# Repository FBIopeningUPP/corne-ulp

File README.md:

# AERIX-ULP

AERIX-ULP is a low-profile split mechanical keyboard with a custom layout.
It is designed around Cherry MX Ultra Low Profile switches and uses a separate
wireless controller and battery-powered electronics on each half.

The board includes:

- 42 keys with per-key diodes
- Wireless nRF52 modules
- USB-C charging and programming
- Separate Li-Po battery support for each half
- 3.0 V regulation
- LCD connectors
- SWD programming and test points
- No 3D-printed case; the underside uses rubber grip dots

AERIX-ULP is a custom keyboard design rather than a Corne-layout derivative.
This project includes the schematics, PCB layout, component library, and
schematics, PCB layout, component library, and production files.

## Board views

- [Main schematic source](hardware/split/split.kicad_sch)
- [Left-half schematic source](hardware/split/left.kicad_sch)
- [Right-half schematic source](hardware/split/right.kicad_sch)
- [Switch matrix schematic source](hardware/split/switch.kicad_sch)
- [PCB layout source](hardware/split/split.kicad_pcb)

schematics and layout.

## Hardware Development

1. Open the KiCad project in `hardware/split/`.
2. Review the custom-layout schematics and PCB layout.
3. Continue placement, routing, and electrical validation in KiCad.
4. Generate fabrication files when the hardware design is ready.
5. Use the production BOM and placement files for assembly.

## Assembly and first power-up

1. Assemble one half and check component orientation.
2. Inspect for solder bridges and shorts.
3. Power it from USB with the battery disconnected.
4. Check `VDD_SYS` and the 3.0 V rail.
5. Connect the battery after the rail check passes.
6. Flash ZMK over SWD and test every key.
7. Repeat for the other half, then test pairing and the inter-half connection.

### Firmware flashing over SWD

Use a 3.3 V-compatible J-Link or CMSIS-DAP probe.

1. Connect `VTref`, `GND`, `SWDIO`, `SWCLK`, and `nRESET` to the matching
   `VDD_SYS`, `GND`, `SWDIO`, `SWDCLK`, and `RESET` test points.
2. Build ZMK and place the generated `firmware.hex` beside `nrfjprog`.
3. Power the half and run:

   ```text
   nrfjprog --program firmware.hex --verify --reset
   ```

Repeat for the other half.

## Source Files

- **Main schematic:** `hardware/split/split.kicad_sch`
- **Left-side schematic:** `hardware/split/left.kicad_sch`
- **Right-side schematic:** `hardware/split/right.kicad_sch`
- **Switch schematic:** `hardware/split/switch.kicad_sch`
- **PCB layout:** `hardware/split/split.kicad_pcb`
- **KiCad project:** `hardware/split/split.kicad_pro`
- **Custom symbols and footprints:** `lib/`
- **ZMK firmware:** `firmware/`

## Production Bill of Materials

The production BOM is available here: [production/bom.csv](production/bom.csv).
The placement files are also available in the [`production/`](production/)
folder:

- [designators.csv](production/designators.csv)
- [positions.csv](production/positions.csv)

The BOM contains **33 line items** and **146 individual parts** for one
complete board assembly. It includes both keyboard halves.

| Designator | Footprint | Qty | Value | LCSC Part # / sourcing |
|---|---|---:|---|---|
| C1, C101, C104, C105, C4, C5 | 0603 | 6 | 100n | [LCSC search](https://www.lcsc.com/search?q=0603%20100nF) |
| C102, C109, C2, C9 | 0603 | 4 | 2.2uF | [LCSC search](https://www.lcsc.com/search?q=0603%202.2uF) |
| C103, C3 | CAP-SMD_L1.6-W0.8-RD | 2 | 4.7uF 6.3V polymer tantalum | [C2158419](https://www.lcsc.com/product-detail/C2158419.html) |
| C106, C107, C6, C7 | 0402 | 4 | 1uF | [LCSC search](https://www.lcsc.com/search?q=0402%201uF) |
| C108, C8 | 0402 | 2 | 560pF | [LCSC search](https://www.lcsc.com/search?q=0402%20560pF) |
| D1, D101 | SOD-323_L1.7-W1.3-LS2.7-RD | 2 | 1N5819WS | [C489147](https://www.lcsc.com/product-detail/C489147.html) |
| D2-D22, D102-D122 | SOD-523_L1.2-W0.8-LS1.6-RD | 42 | 1N4148WT-7 | [C83482](https://www.lcsc.com/product-detail/C83482.html) |
| J1, J101 | FFC-SMD_10P-P0.50_FH34SRJ-10S-0.5SH | 2 | LS011B7DH03_FPC | [C324723](https://www.lcsc.com/product-detail/C324723.html) |
| OSC1, OSC101 | OSC-SMD_4P-L3.2-W1.5 | 2 | X1B0002110001 | [C256005](https://www.lcsc.com/product-detail/C256005.html) |
| Q2, Q102 | SOT-23-3_L3.0-W1.7-P0.95-LS2.9-BR | 2 | AO3407 | [C351408](https://www.lcsc.com/product-detail/C351408.html) |
| R1, R101, R102, R2 | 0402 | 4 | 5.1k | [LCSC search](https://www.lcsc.com/search?q=0402%205.1k) |
| R3, R8, R103, R108 | 0402 | 4 | 100k | [LCSC search](https://www.lcsc.com/search?q=0402%20100k) |
| R4, R104 | 0402 | 2 | 33.2k | [LCSC search](https://www.lcsc.com/search?q=0402%2033.2k) |
| R6, R7, R106, R107 | 0402 | 4 | 820k | [LCSC search](https://www.lcsc.com/search?q=0402%20820k) |
| SW1-SW21, SW101-SW121 | Cherry_ULP_SMD | 42 | Cherry_ULP_SMD | [Cherry MX ULP](https://www.cherry.de/en-us/products/switches/mx-ultra-low-profile) |
| TP1 | TestPoint_Pad_D1.5mm | 1 | L_VDD_SYS | [LCSC search](https://www.lcsc.com/search?q=1.5mm%20test%20point%20pad) |
| TP2, TP7 | TestPoint_Pad_D1.5mm | 2 | L_GND | [LCSC search](https://www.lcsc.com/search?q=1.5mm%20test%20point%20pad) |
| TP3 | TestPoint_Pad_D1.5mm | 1 | L_SWDIO | [LCSC search](https://www.lcsc.com/search?q=1.5mm%20test%20point%20pad) |
| TP4 | TestPoint_Pad_D1.5mm | 1 | L_SWDCLK | [LCSC search](https://www.lcsc.com/search?q=1.5mm%20test%20point%20pad) |
| TP5 | TestPoint_Pad_D1.5mm | 1 | L_RESET | [LCSC search](https://www.lcsc.com/search?q=1.5mm%20test%20point%20pad) |
| TP6 | TestPoint_Pad_D2.0mm | 1 | L_VBAT | [LCSC search](https://www.lcsc.com/search?q=2mm%20test%20point%20pad) |
| TP101 | TestPoint_Pad_D1.5mm | 1 | R_VDD_SYS | [LCSC search](https://www.lcsc.com/search?q=1.5mm%20test%20point%20pad) |
| TP102, TP107 | TestPoint_Pad_D1.5mm | 2 | R_GND | [LCSC search](https://www.lcsc.com/search?q=1.5mm%20test%20point%20pad) |
| TP103 | TestPoint_Pad_D1.5mm | 1 | R_SWDIO | [LCSC search](https://www.lcsc.com/search?q=1.5mm%20test%20point%20pad) |
| TP104 | TestPoint_Pad_D1.5mm | 1 | R_SWDCLK | [LCSC search](https://www.lcsc.com/search?q=1.5mm%20test%20point%20pad) |
| TP105 | TestPoint_Pad_D1.5mm | 1 | R_RESET | [LCSC search](https://www.lcsc.com/search?q=1.5mm%20test%20point%20pad) |
| TP106 | TestPoint_Pad_D2.0mm | 1 | R_VBAT | [LCSC search](https://www.lcsc.com/search?q=2mm%20test%20point%20pad) |
| U1, U101 | WIRELM-SMD_E73-2G4M08S1C | 2 | E73-2G4M08S1C | [C356849](https://www.lcsc.com/product-detail/C356849.html) |
| U2, U102 | SOT-23-5_L3.0-W1.7-P0.95-LS2.8-BL | 2 | TP4054 | [C32574](https://www.lcsc.com/product-detail/C32574.html) |
| U3, U103 | SOT-23-5 | 2 | MIC5219-3.0YM5 | [LCSC search](https://www.lcsc.com/search?q=MIC5219-3.0YM5) |
| USB1, USB101 | USB-C-SMD_SHOU_TYPE-C-16P-CB1.6 | 2 | TYPE-C 16P CB1.6 073 | [C2906290](https://www.lcsc.com/product-detail/C2906290.html) |

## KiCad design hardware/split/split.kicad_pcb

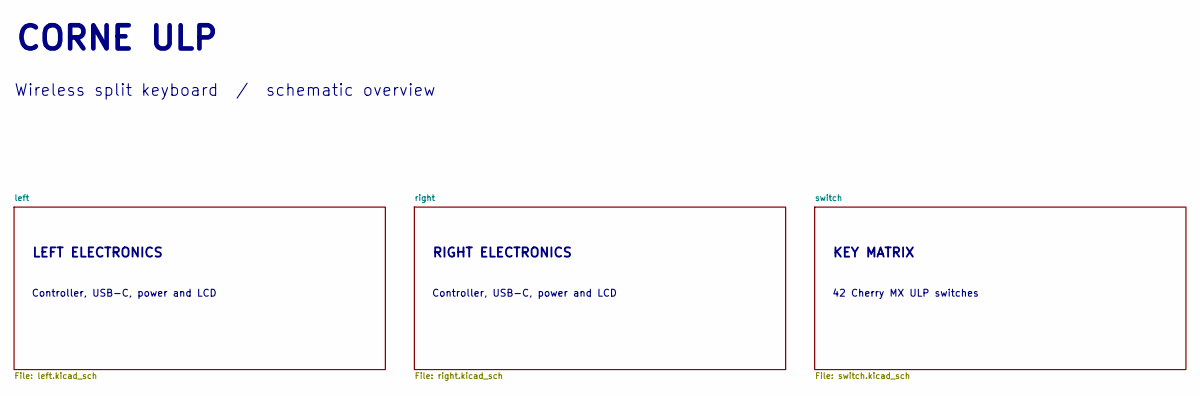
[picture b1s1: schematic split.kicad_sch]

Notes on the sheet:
Controller, USB-C, power and LCD
CORNE ULP
42 Cherry MX ULP switches
Wireless split keyboard / schematic overview
RIGHT ELECTRONICS
LEFT ELECTRONICS
KEY MATRIX

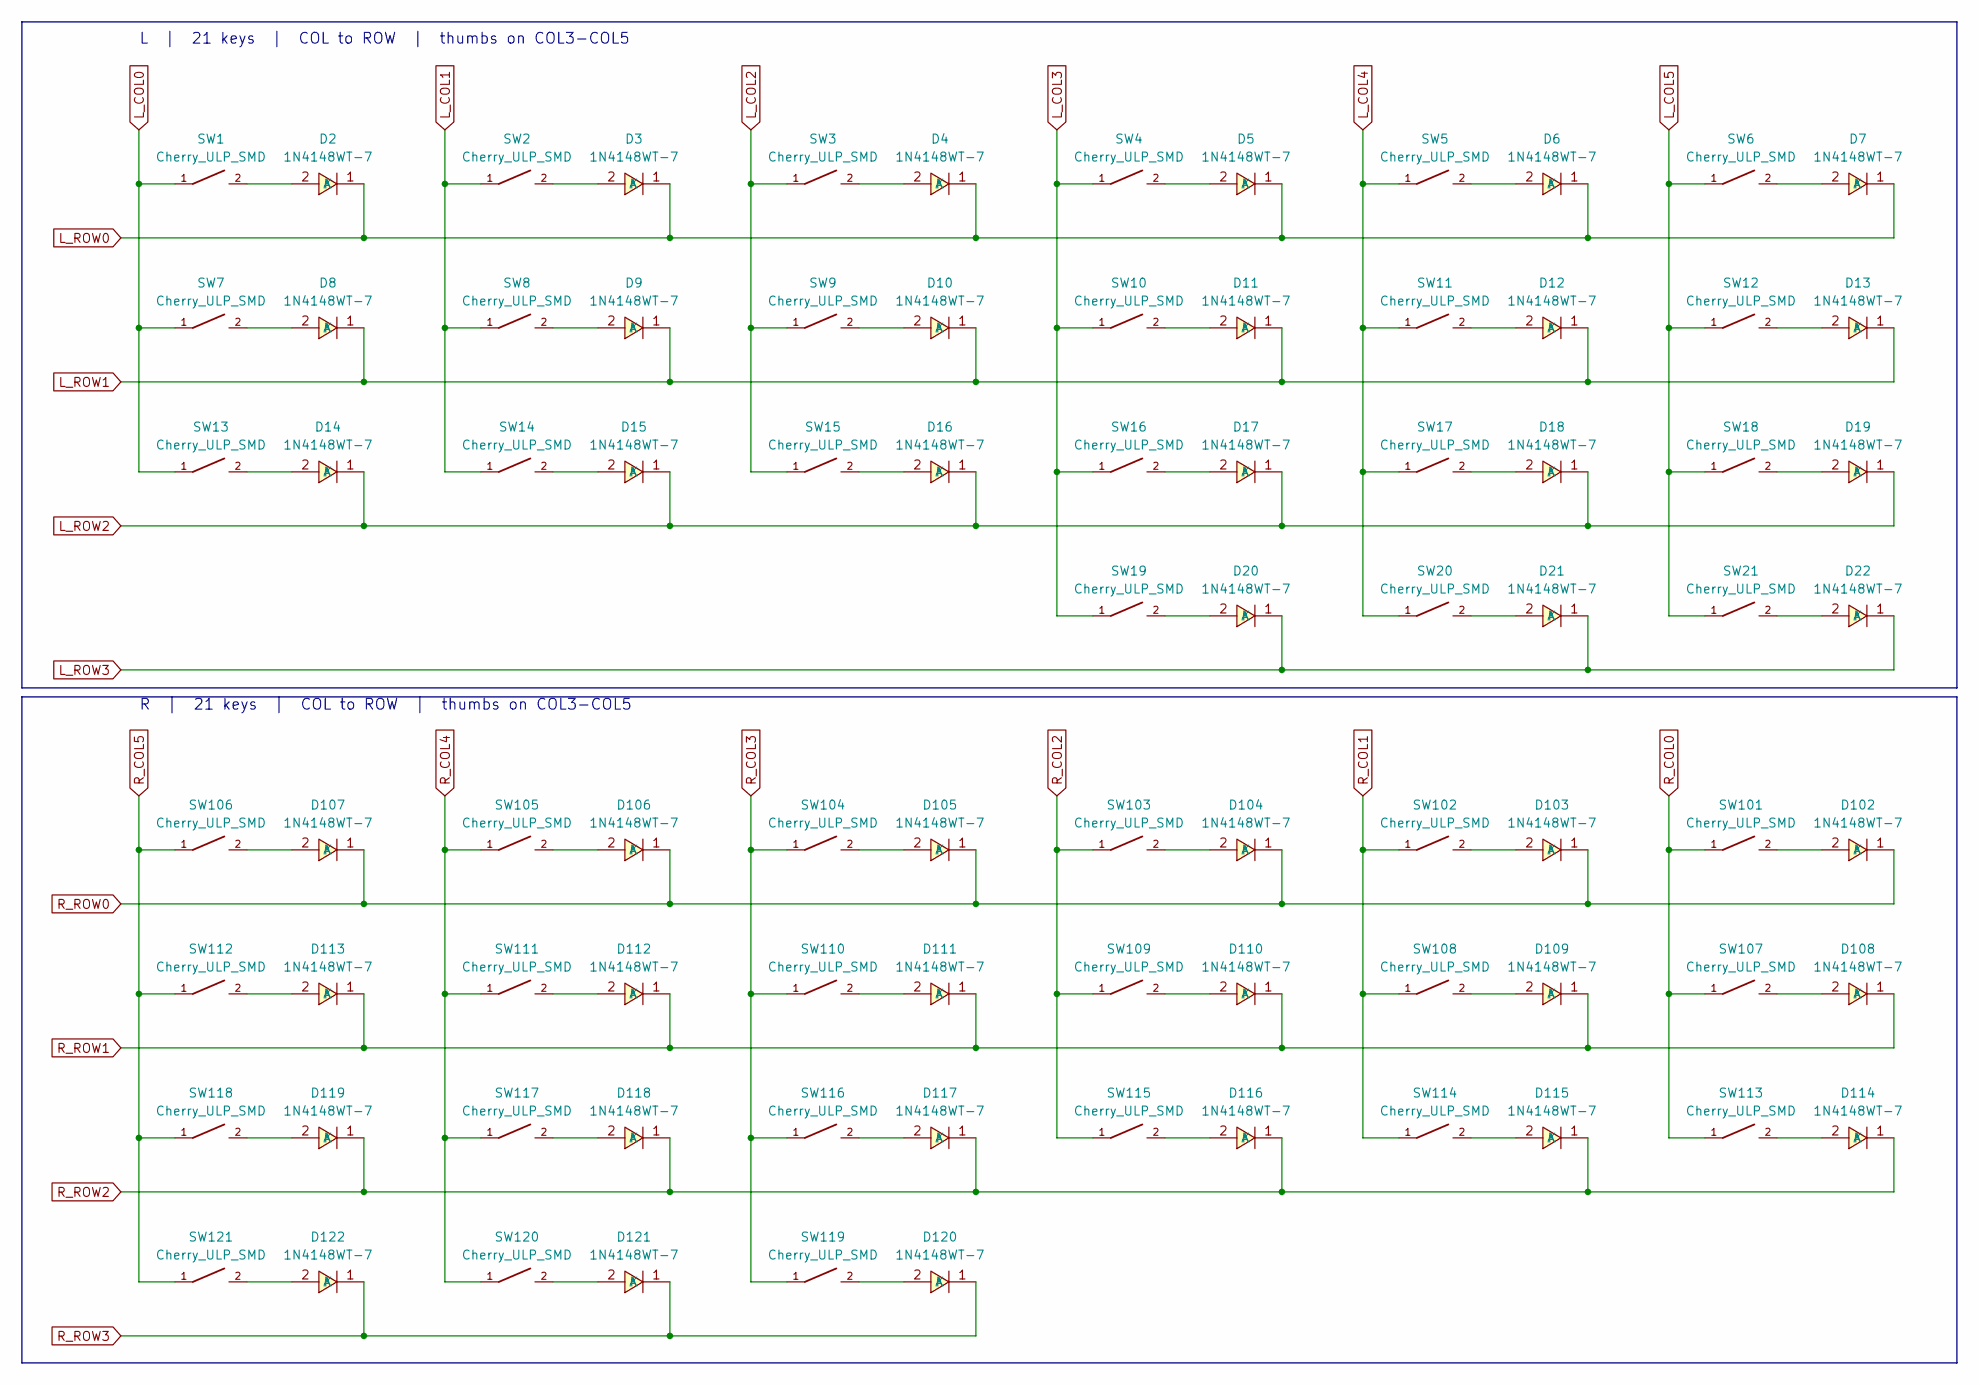
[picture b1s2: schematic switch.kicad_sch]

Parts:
D2, D3, D4, D5, D6, D7, D8, D9, D10, D11, D12, D13, D14, D15, D16, D17, D18, D19, D20, D21, D22, D102, D103, D104, D105, D106, D107, D108, D109, D110, D111, D112, D113, D114, D115, D116, D117, D118, D119, D120, D121, D122: 1N4148WT-7; SOD-523_L1.2-W0.8-LS1.6-RD
SW1, SW2, SW3, SW4, SW5, SW6, SW7, SW8, SW9, SW10, SW11, SW12, SW13, SW14, SW15, SW16, SW17, SW18, SW19, SW20, SW21, SW101, SW102, SW103, SW104, SW105, SW106, SW107, SW108, SW109, SW110, SW111, SW112, SW113, SW114, SW115, SW116, SW117, SW118, SW119, SW120, SW121: Cherry_ULP_SMD

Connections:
L_COL0: SW1.1, SW7.1, SW13.1; also elsewhere on the board
L_COL1: SW2.1, SW8.1, SW14.1; also elsewhere on the board
L_COL2: SW3.1, SW9.1, SW15.1; also elsewhere on the board
L_COL3: SW4.1, SW10.1, SW16.1, SW19.1; also elsewhere on the board
L_COL4: SW5.1, SW11.1, SW17.1, SW20.1; also elsewhere on the board
L_COL5: SW6.1, SW12.1, SW18.1, SW21.1; also elsewhere on the board
L_ROW0: D2.1 (K), D3.1 (K), D4.1 (K), D5.1 (K), D6.1 (K), D7.1 (K); also elsewhere on the board
L_ROW1: D8.1 (K), D9.1 (K), D10.1 (K), D11.1 (K), D12.1 (K), D13.1 (K); also elsewhere on the board
L_ROW2: D14.1 (K), D15.1 (K), D16.1 (K), D17.1 (K), D18.1 (K), D19.1 (K); also elsewhere on the board
L_ROW3: D20.1 (K), D21.1 (K), D22.1 (K); also elsewhere on the board
unnamed: D2.2 (A), SW1.2
unnamed: D3.2 (A), SW2.2
unnamed: D4.2 (A), SW3.2
unnamed: D5.2 (A), SW4.2
unnamed: D6.2 (A), SW5.2
unnamed: D7.2 (A), SW6.2
unnamed: D8.2 (A), SW7.2
unnamed: D9.2 (A), SW8.2
unnamed: D10.2 (A), SW9.2
unnamed: D11.2 (A), SW10.2
unnamed: D12.2 (A), SW11.2
unnamed: D13.2 (A), SW12.2
unnamed: D14.2 (A), SW13.2
unnamed: D15.2 (A), SW14.2
unnamed: D16.2 (A), SW15.2
unnamed: D17.2 (A), SW16.2
unnamed: D18.2 (A), SW17.2
unnamed: D19.2 (A), SW18.2
unnamed: D20.2 (A), SW19.2
unnamed: D21.2 (A), SW20.2
unnamed: D22.2 (A), SW21.2
unnamed: D102.2 (A), SW101.2
unnamed: D103.2 (A), SW102.2
unnamed: D104.2 (A), SW103.2
unnamed: D105.2 (A), SW104.2
unnamed: D106.2 (A), SW105.2
unnamed: D107.2 (A), SW106.2
unnamed: D108.2 (A), SW107.2
unnamed: D109.2 (A), SW108.2
unnamed: D110.2 (A), SW109.2
unnamed: D111.2 (A), SW110.2
unnamed: D112.2 (A), SW111.2
unnamed: D113.2 (A), SW112.2
unnamed: D114.2 (A), SW113.2
unnamed: D115.2 (A), SW114.2
unnamed: D116.2 (A), SW115.2
unnamed: D117.2 (A), SW116.2
unnamed: D118.2 (A), SW117.2
unnamed: D119.2 (A), SW118.2
unnamed: D120.2 (A), SW119.2
unnamed: D121.2 (A), SW120.2
unnamed: D122.2 (A), SW121.2
R_COL0: SW101.1, SW107.1, SW113.1; also elsewhere on the board
R_COL1: SW102.1, SW108.1, SW114.1; also elsewhere on the board
R_COL2: SW103.1, SW109.1, SW115.1; also elsewhere on the board
R_COL3: SW104.1, SW110.1, SW116.1, SW119.1; also elsewhere on the board
R_COL4: SW105.1, SW111.1, SW117.1, SW120.1; also elsewhere on the board
R_COL5: SW106.1, SW112.1, SW118.1, SW121.1; also elsewhere on the board
R_ROW0: D102.1 (K), D103.1 (K), D104.1 (K), D105.1 (K), D106.1 (K), D107.1 (K); also elsewhere on the board
R_ROW1: D108.1 (K), D109.1 (K), D110.1 (K), D111.1 (K), D112.1 (K), D113.1 (K); also elsewhere on the board
R_ROW2: D114.1 (K), D115.1 (K), D116.1 (K), D117.1 (K), D118.1 (K), D119.1 (K); also elsewhere on the board
R_ROW3: D120.1 (K), D121.1 (K), D122.1 (K); also elsewhere on the board

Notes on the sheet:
L | 21 keys | COL to ROW | thumbs on COL3-COL5
R | 21 keys | COL to ROW | thumbs on COL3-COL5

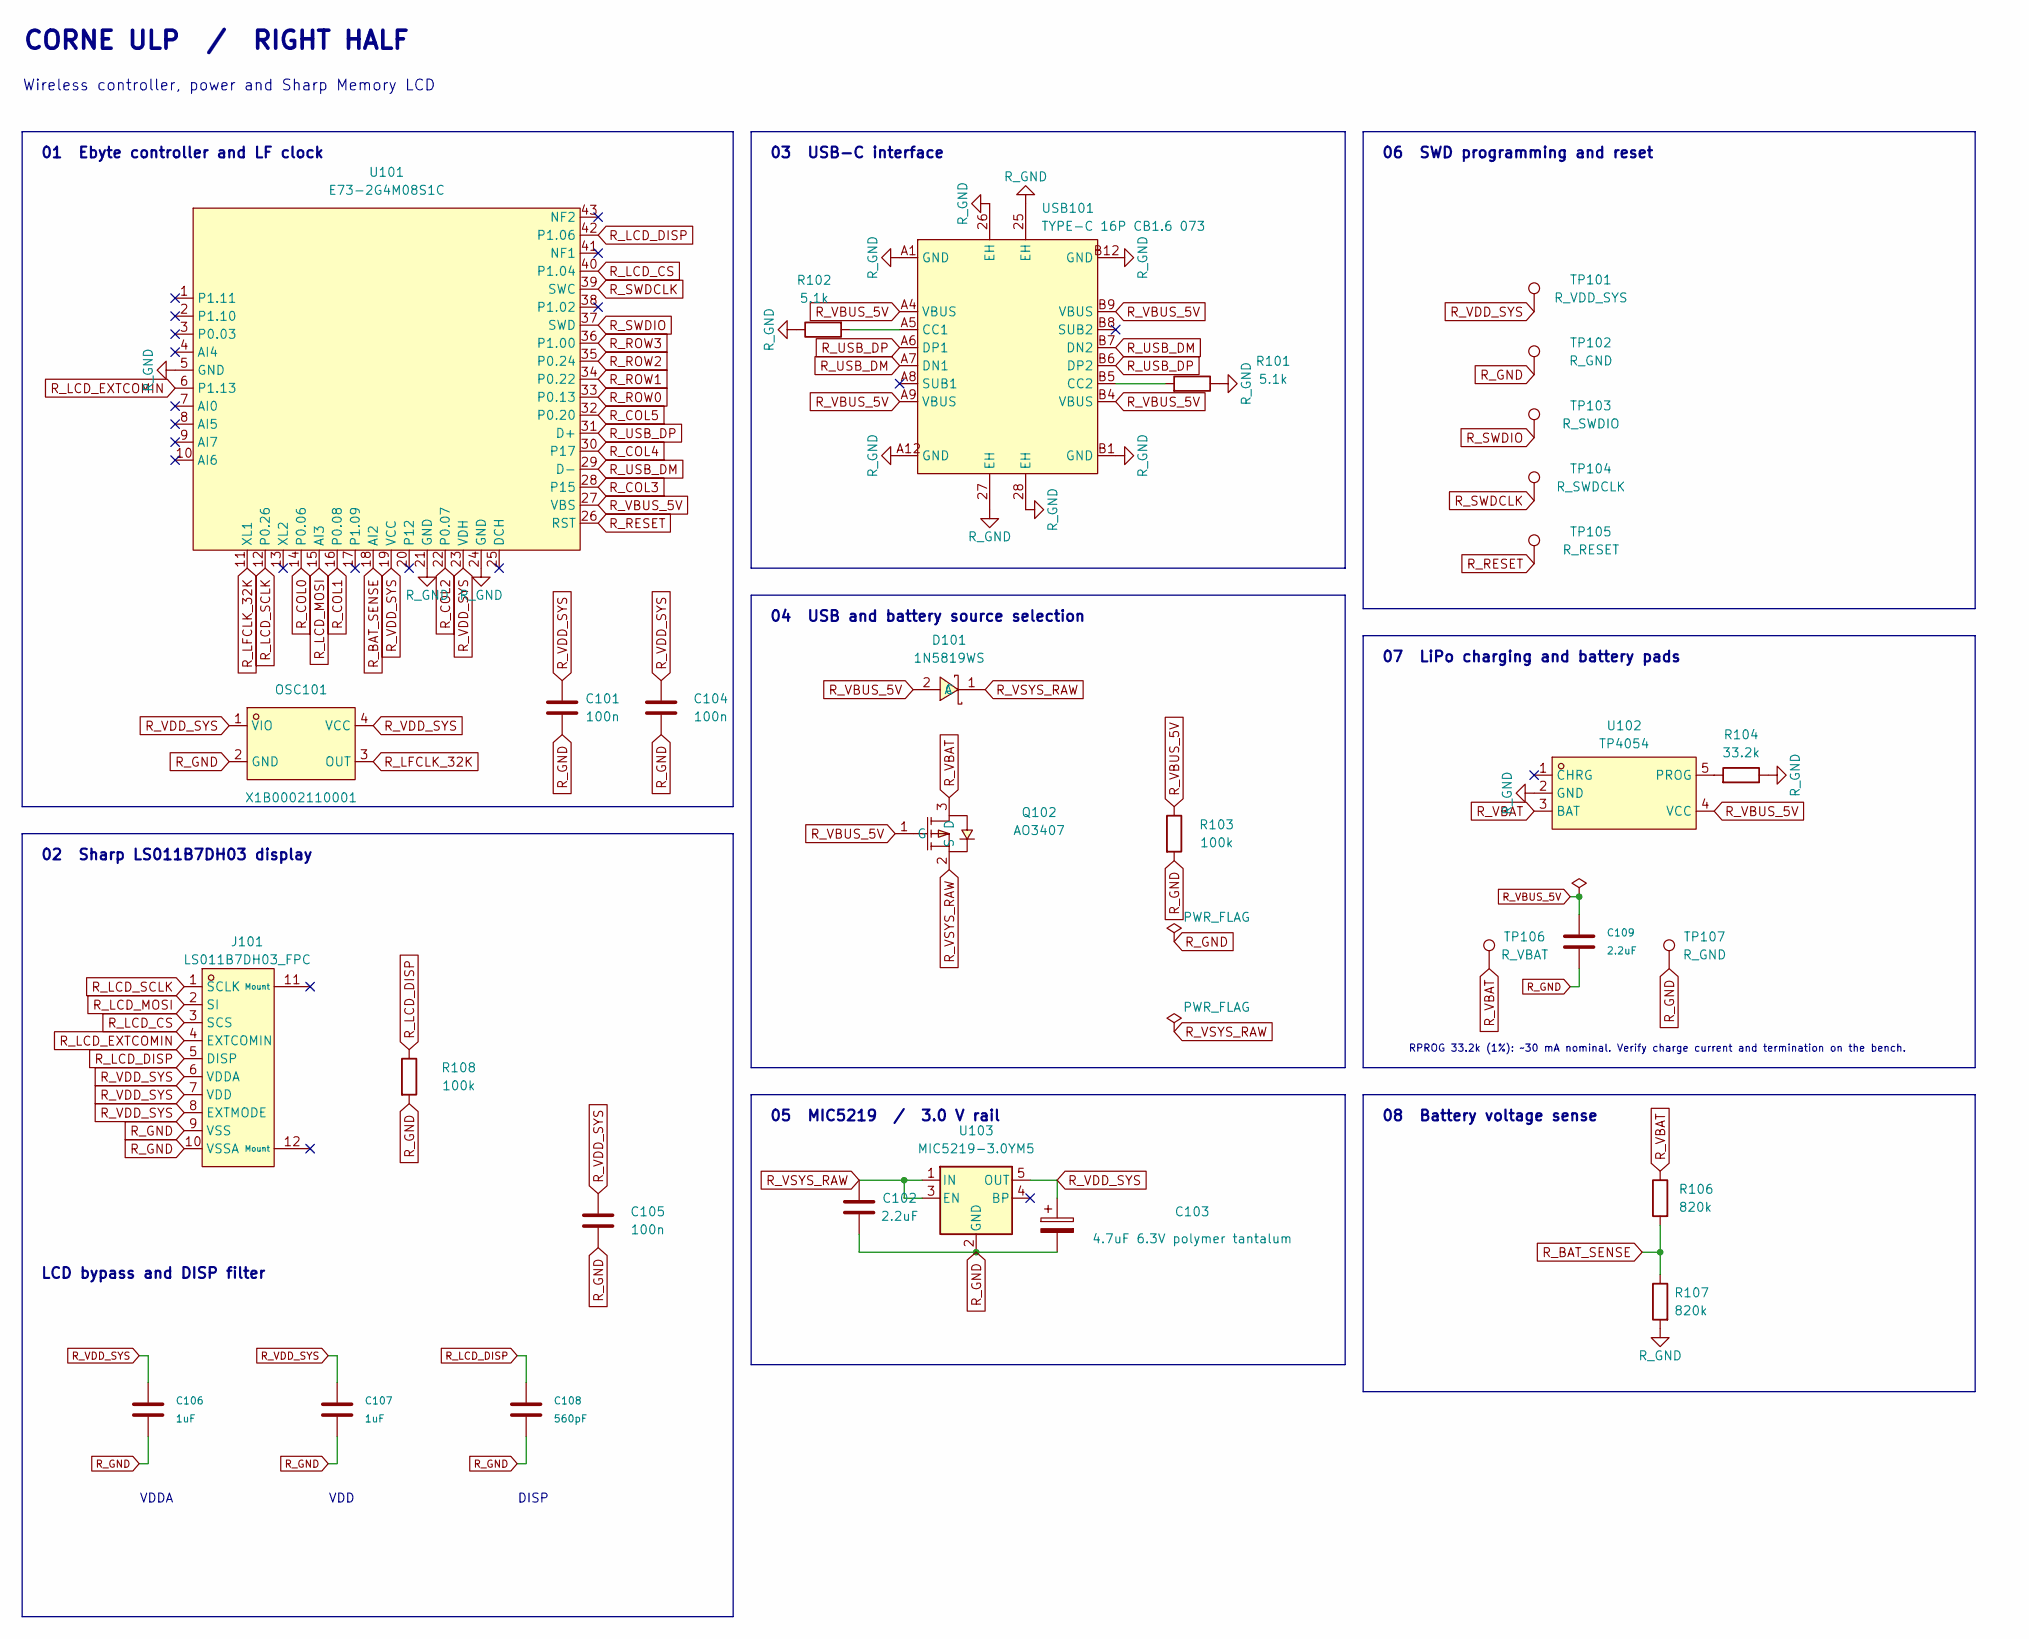
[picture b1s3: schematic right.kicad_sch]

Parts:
C101, C104, C105: 100n; C_0603_1608Metric
C102, C109: 2.2uF; C_0603_1608Metric
C103: 4.7uF 6.3V polymer tantalum; CAP-SMD_L1.6-W0.8-RD; MPN T55J475M6R3C0500
C106, C107: 1uF; C_0402_1005Metric
C108: 560pF; C_0402_1005Metric
D101: 1N5819WS; SOD-323_L1.7-W1.3-LS2.7-RD
J101: LS011B7DH03_FPC; FFC-SMD_10P-P0.50_FH34SRJ-10S-0.5SH
OSC101: X1B0002110001; OSC-SMD_4P-L3.2-W1.5
Q102: AO3407; SOT-23-3_L3.0-W1.7-P0.95-LS2.9-BR
R101, R102: 5.1k; R_0402_1005Metric
R103, R108: 100k; R_0402_1005Metric
R104: 33.2k; R_0402_1005Metric
R106, R107: 820k; R_0402_1005Metric
TP101: R_VDD_SYS; TestPoint_Pad_D1.5mm
TP102: R_GND; TestPoint_Pad_D1.5mm
TP103: R_SWDIO; TestPoint_Pad_D1.5mm
TP104: R_SWDCLK; TestPoint_Pad_D1.5mm
TP105: R_RESET; TestPoint_Pad_D1.5mm
TP106: R_VBAT; TestPoint_Pad_D2.0mm
TP107: R_GND; TestPoint_Pad_D2.0mm
U101: E73-2G4M08S1C; WIRELM-SMD_E73-2G4M08S1C; MPN E73-2G4M08S1C; LCSC Part C356849
U102: TP4054; SOT-23-5_L3.0-W1.7-P0.95-LS2.8-BL; MPN TP4054-42-SOT25R; LCSC Part C32574
U103: MIC5219-3.0YM5; SOT-23-5
USB101: TYPE-C 16P CB1.6 073; USB-C-SMD_SHOU_TYPE-C-16P-CB1.6; MPN TYPE-C 16P CB1.6 073; LCSC Part C2906290

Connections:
unnamed: R104.1, U102.5 (PROG)
unnamed: R102.1, USB101.A5 (CC1)
unnamed: R101.1, USB101.B5 (CC2)
R_BAT_SENSE: R106.1, R107.2, U101.18 (AI2)
R_COL0: U101.14 (P0.06); also elsewhere on the board
R_COL1: U101.16 (P0.08); also elsewhere on the board
R_COL2: U101.22 (P0.07); also elsewhere on the board
R_COL3: U101.28 (P15); also elsewhere on the board
R_COL4: U101.30 (P17); also elsewhere on the board
R_COL5: U101.32 (P0.20); also elsewhere on the board
R_GND: C101.2, C102.2, C103.2, C104.2, C105.2, C106.2, C107.2, C108.2, C109.2, J101.9 (VSS), J101.10 (VSSA), OSC101.2 (GND), R101.2, R102.2, R103.2, R104.2, R107.1, R108.2, TP102.1 (1_1), TP107.1 (1_1), U101.5 (GND), U101.21 (GND), U101.24 (GND), U102.2 (GND), U103.2 (GND), USB101.25 (EH), USB101.26 (EH), USB101.27 (EH), USB101.28 (EH), USB101.A1 (GND), USB101.A12 (GND), USB101.B1 (GND), USB101.B12 (GND)
R_LCD_CS: J101.3 (SCS), U101.40 (P1.04)
R_LCD_DISP: C108.1, J101.5 (DISP), R108.1, U101.42 (P1.06)
R_LCD_EXTCOMIN: J101.4 (EXTCOMIN), U101.6 (P1.13)
R_LCD_MOSI: J101.2 (SI), U101.15 (AI3)
R_LCD_SCLK: J101.1 (SCLK), U101.12 (P0.26)
R_LFCLK_32K: OSC101.3 (OUT), U101.11 (XL1)
R_RESET: TP105.1 (1_1), U101.26 (RST)
R_ROW0: U101.33 (P0.13); also elsewhere on the board
R_ROW1: U101.34 (P0.22); also elsewhere on the board
R_ROW2: U101.35 (P0.24); also elsewhere on the board
R_ROW3: U101.36 (P1.00); also elsewhere on the board
R_SWDCLK: TP104.1 (1_1), U101.39 (SWC)
R_SWDIO: TP103.1 (1_1), U101.37 (SWD)
R_USB_DM: U101.29 (D-), USB101.A7 (DN1), USB101.B7 (DN2)
R_USB_DP: U101.31 (D+), USB101.A6 (DP1), USB101.B6 (DP2)
R_VBAT: Q102.3 (D), R106.2, TP106.1 (1_1), U102.3 (BAT)
R_VBUS_5V: C109.1, D101.2 (A), Q102.1 (G), R103.1, U101.27 (VBS), U102.4 (VCC), USB101.A4 (VBUS), USB101.A9 (VBUS), USB101.B4 (VBUS), USB101.B9 (VBUS)
R_VDD_SYS: C101.1, C103.1, C104.1, C105.1, C106.1, C107.1, J101.6 (VDDA), J101.7 (VDD), J101.8 (EXTMODE), OSC101.1 (VIO), OSC101.4 (VCC), TP101.1 (1_1), U101.19 (VCC), U101.23 (VDH), U103.5 (OUT)
R_VSYS_RAW: C102.1, D101.1 (C), Q102.2 (S), U103.1 (IN), U103.3 (EN)

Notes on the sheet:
06 SWD programming and reset
VDD
04 USB and battery source selection
LCD bypass and DISP filter
02 Sharp LS011B7DH03 display
08 Battery voltage sense
Wireless controller, power and Sharp Memory LCD
01 Ebyte controller and LF clock
VDDA
03 USB-C interface
DISP
RPROG 33.2k (1%): ~30 mA nominal. Verify charge current and termination on the bench.
CORNE ULP / RIGHT HALF
07 LiPo charging and battery pads
05 MIC5219 / 3.0 V rail

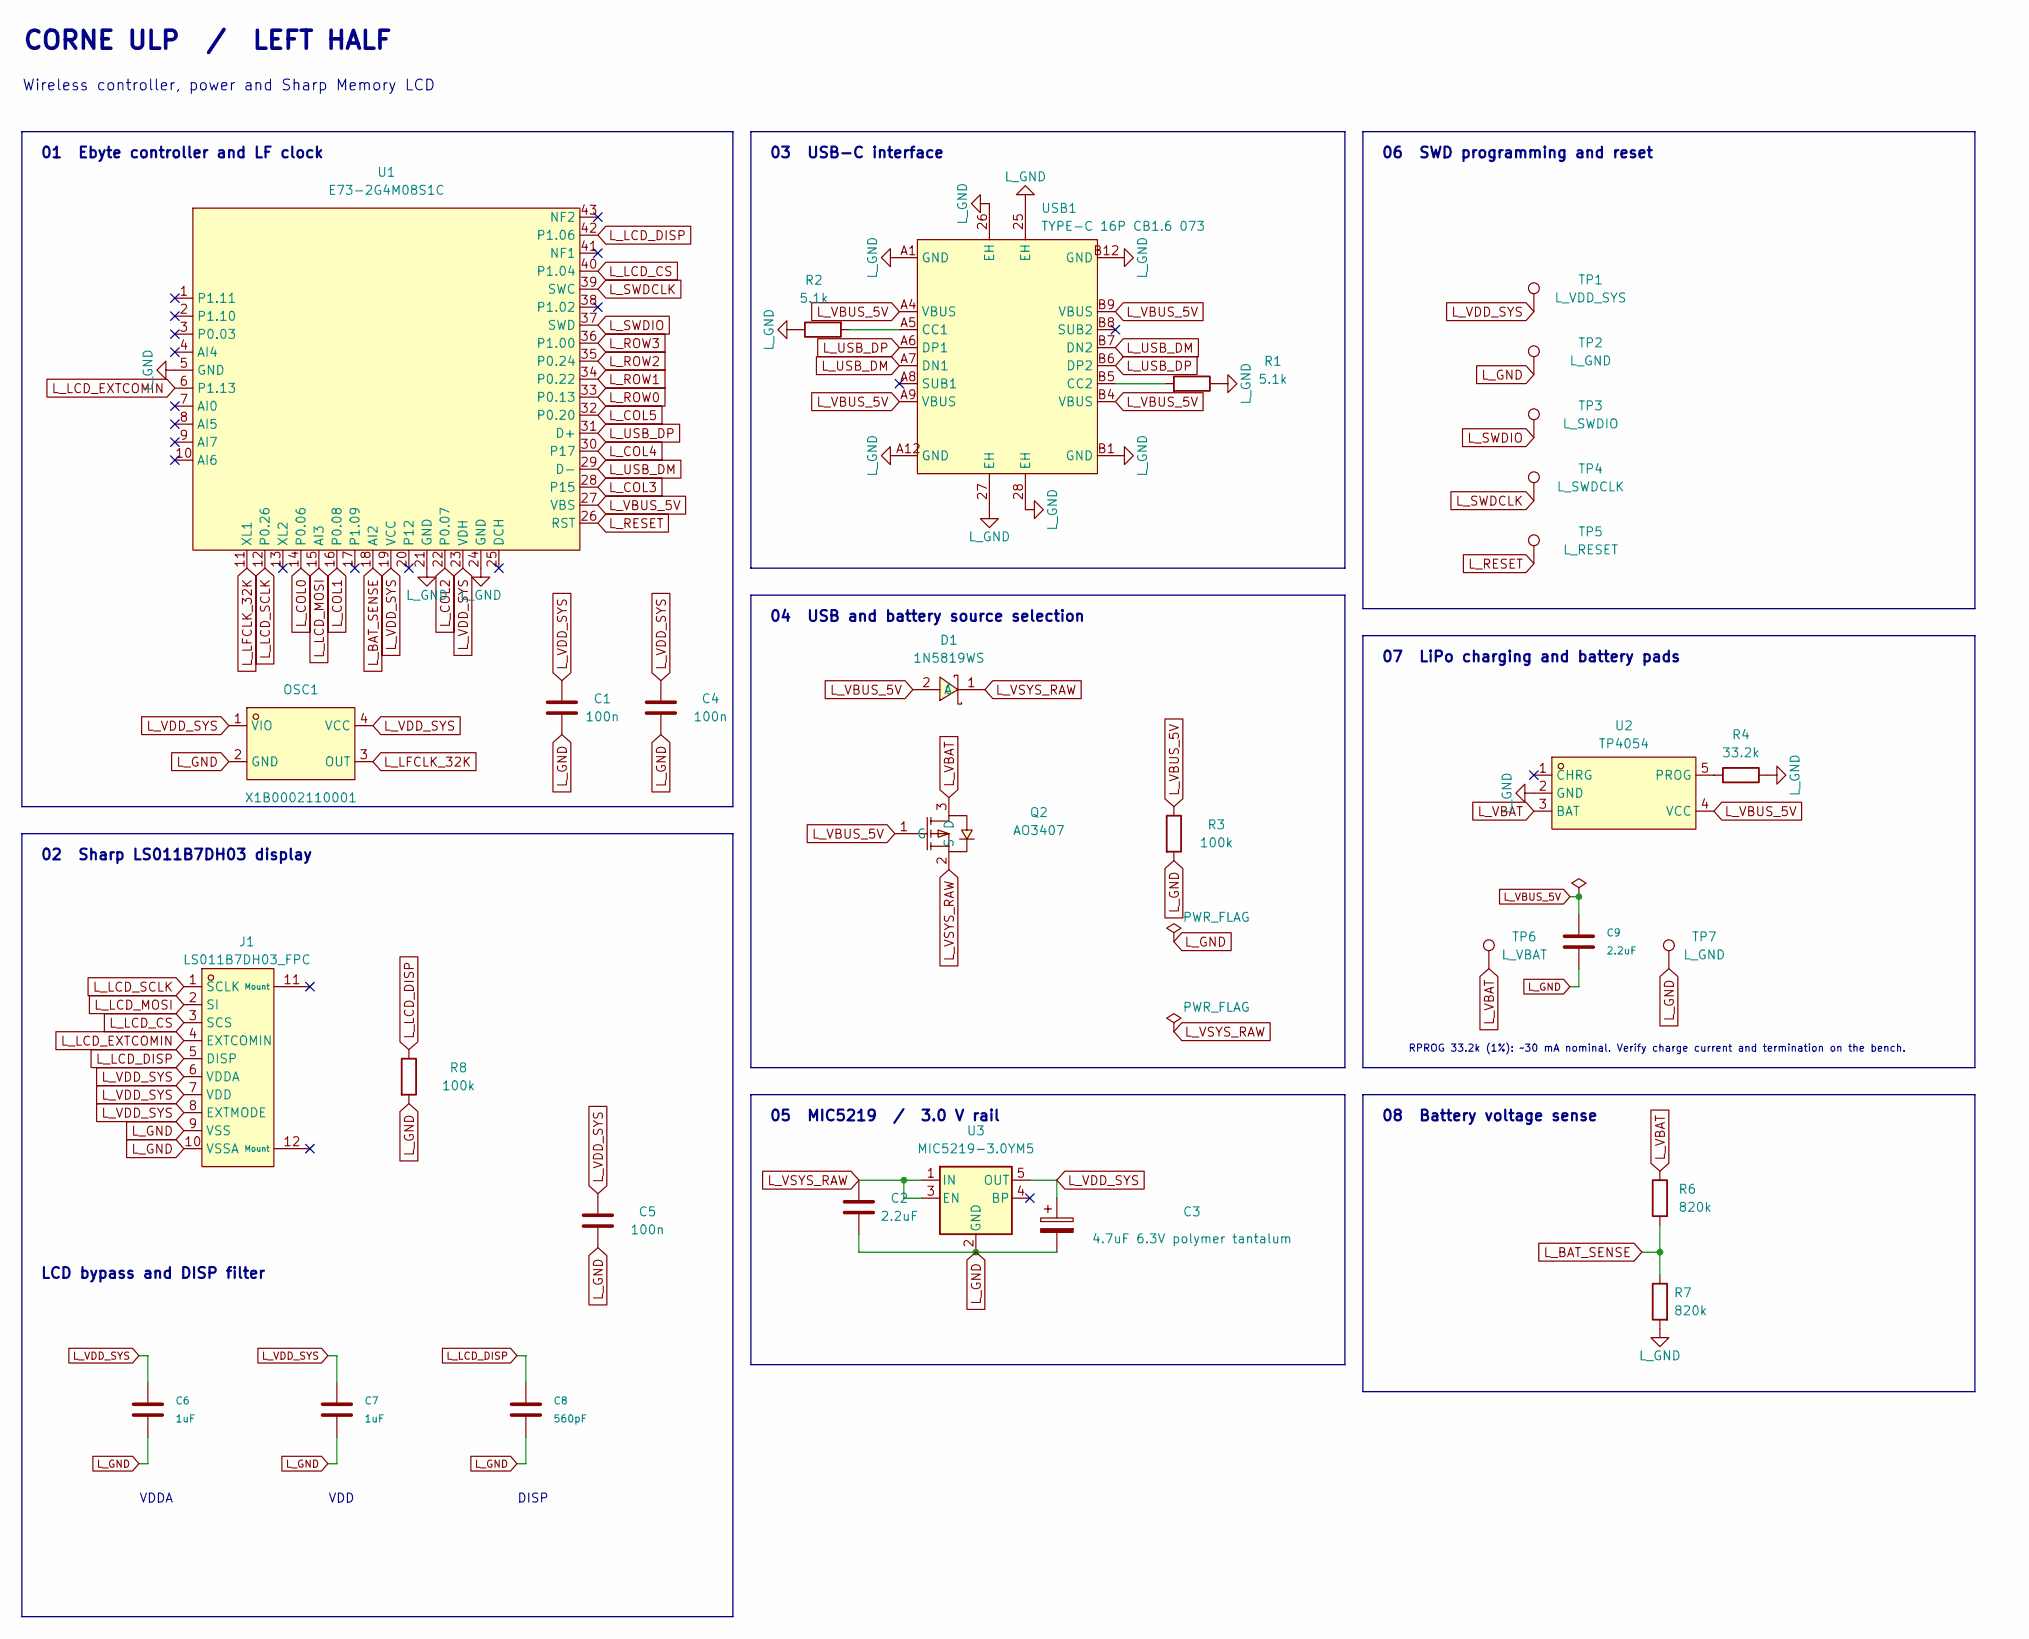
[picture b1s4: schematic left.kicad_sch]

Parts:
C1, C4, C5: 100n; C_0603_1608Metric
C2, C9: 2.2uF; C_0603_1608Metric
C3: 4.7uF 6.3V polymer tantalum; CAP-SMD_L1.6-W0.8-RD; MPN T55J475M6R3C0500
C6, C7: 1uF; C_0402_1005Metric
C8: 560pF; C_0402_1005Metric
D1: 1N5819WS; SOD-323_L1.7-W1.3-LS2.7-RD
J1: LS011B7DH03_FPC; FFC-SMD_10P-P0.50_FH34SRJ-10S-0.5SH
OSC1: X1B0002110001; OSC-SMD_4P-L3.2-W1.5
Q2: AO3407; SOT-23-3_L3.0-W1.7-P0.95-LS2.9-BR
R1, R2: 5.1k; R_0402_1005Metric
R3, R8: 100k; R_0402_1005Metric
R4: 33.2k; R_0402_1005Metric
R6, R7: 820k; R_0402_1005Metric
TP1: L_VDD_SYS; TestPoint_Pad_D1.5mm
TP2: L_GND; TestPoint_Pad_D1.5mm
TP3: L_SWDIO; TestPoint_Pad_D1.5mm
TP4: L_SWDCLK; TestPoint_Pad_D1.5mm
TP5: L_RESET; TestPoint_Pad_D1.5mm
TP6: L_VBAT; TestPoint_Pad_D2.0mm
TP7: L_GND; TestPoint_Pad_D2.0mm
U1: E73-2G4M08S1C; WIRELM-SMD_E73-2G4M08S1C; MPN E73-2G4M08S1C; LCSC Part C356849
U2: TP4054; SOT-23-5_L3.0-W1.7-P0.95-LS2.8-BL; MPN TP4054-42-SOT25R; LCSC Part C32574
U3: MIC5219-3.0YM5; SOT-23-5
USB1: TYPE-C 16P CB1.6 073; USB-C-SMD_SHOU_TYPE-C-16P-CB1.6; MPN TYPE-C 16P CB1.6 073; LCSC Part C2906290

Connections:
L_BAT_SENSE: R6.1, R7.2, U1.18 (AI2)
L_COL0: U1.14 (P0.06); also elsewhere on the board
L_COL1: U1.16 (P0.08); also elsewhere on the board
L_COL2: U1.22 (P0.07); also elsewhere on the board
L_COL3: U1.28 (P15); also elsewhere on the board
L_COL4: U1.30 (P17); also elsewhere on the board
L_COL5: U1.32 (P0.20); also elsewhere on the board
L_GND: C1.2, C2.2, C3.2, C4.2, C5.2, C6.2, C7.2, C8.2, C9.2, J1.9 (VSS), J1.10 (VSSA), OSC1.2 (GND), R1.2, R2.2, R3.2, R4.2, R7.1, R8.2, TP2.1 (1_1), TP7.1 (1_1), U1.5 (GND), U1.21 (GND), U1.24 (GND), U2.2 (GND), U3.2 (GND), USB1.25 (EH), USB1.26 (EH), USB1.27 (EH), USB1.28 (EH), USB1.A1 (GND), USB1.A12 (GND), USB1.B1 (GND), USB1.B12 (GND)
L_LCD_CS: J1.3 (SCS), U1.40 (P1.04)
L_LCD_DISP: C8.1, J1.5 (DISP), R8.1, U1.42 (P1.06)
L_LCD_EXTCOMIN: J1.4 (EXTCOMIN), U1.6 (P1.13)
L_LCD_MOSI: J1.2 (SI), U1.15 (AI3)
L_LCD_SCLK: J1.1 (SCLK), U1.12 (P0.26)
L_LFCLK_32K: OSC1.3 (OUT), U1.11 (XL1)
L_RESET: TP5.1 (1_1), U1.26 (RST)
L_ROW0: U1.33 (P0.13); also elsewhere on the board
L_ROW1: U1.34 (P0.22); also elsewhere on the board
L_ROW2: U1.35 (P0.24); also elsewhere on the board
L_ROW3: U1.36 (P1.00); also elsewhere on the board
L_SWDCLK: TP4.1 (1_1), U1.39 (SWC)
L_SWDIO: TP3.1 (1_1), U1.37 (SWD)
L_USB_DM: U1.29 (D-), USB1.A7 (DN1), USB1.B7 (DN2)
L_USB_DP: U1.31 (D+), USB1.A6 (DP1), USB1.B6 (DP2)
L_VBAT: Q2.3 (D), R6.2, TP6.1 (1_1), U2.3 (BAT)
L_VBUS_5V: C9.1, D1.2 (A), Q2.1 (G), R3.1, U1.27 (VBS), U2.4 (VCC), USB1.A4 (VBUS), USB1.A9 (VBUS), USB1.B4 (VBUS), USB1.B9 (VBUS)
L_VDD_SYS: C1.1, C3.1, C4.1, C5.1, C6.1, C7.1, J1.6 (VDDA), J1.7 (VDD), J1.8 (EXTMODE), OSC1.1 (VIO), OSC1.4 (VCC), TP1.1 (1_1), U1.19 (VCC), U1.23 (VDH), U3.5 (OUT)
L_VSYS_RAW: C2.1, D1.1 (C), Q2.2 (S), U3.1 (IN), U3.3 (EN)
unnamed: R4.1, U2.5 (PROG)
unnamed: R2.1, USB1.A5 (CC1)
unnamed: R1.1, USB1.B5 (CC2)

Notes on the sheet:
DISP
01 Ebyte controller and LF clock
VDD
06 SWD programming and reset
VDDA
07 LiPo charging and battery pads
LCD bypass and DISP filter
02 Sharp LS011B7DH03 display
08 Battery voltage sense
RPROG 33.2k (1%): ~30 mA nominal. Verify charge current and termination on the bench.
04 USB and battery source selection
Wireless controller, power and Sharp Memory LCD
CORNE ULP / LEFT HALF
03 USB-C interface
05 MIC5219 / 3.0 V rail

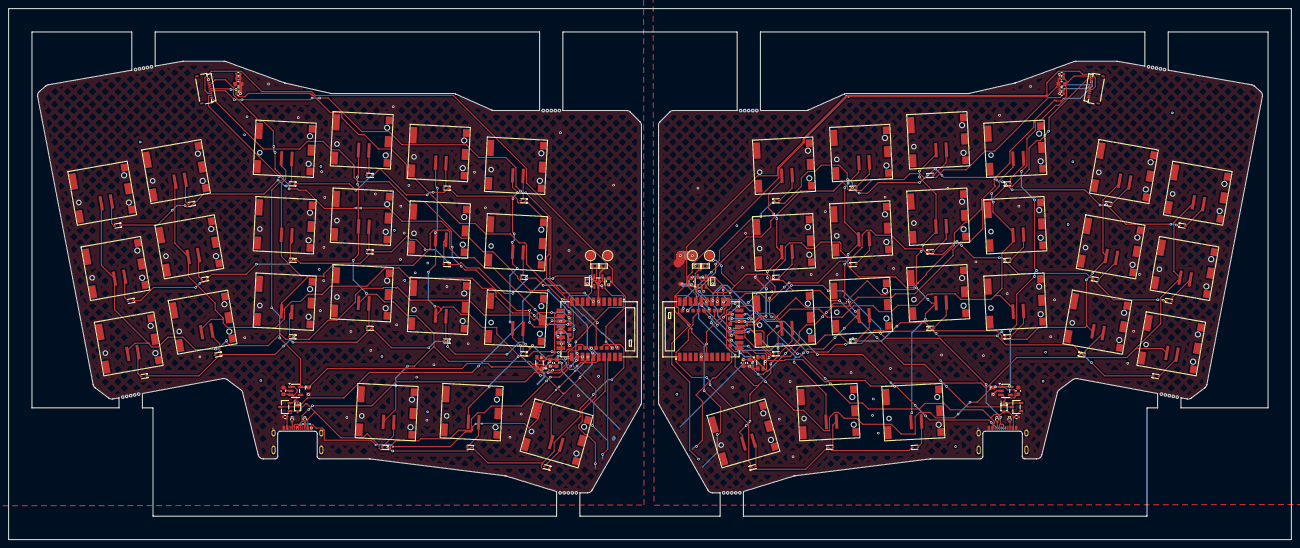
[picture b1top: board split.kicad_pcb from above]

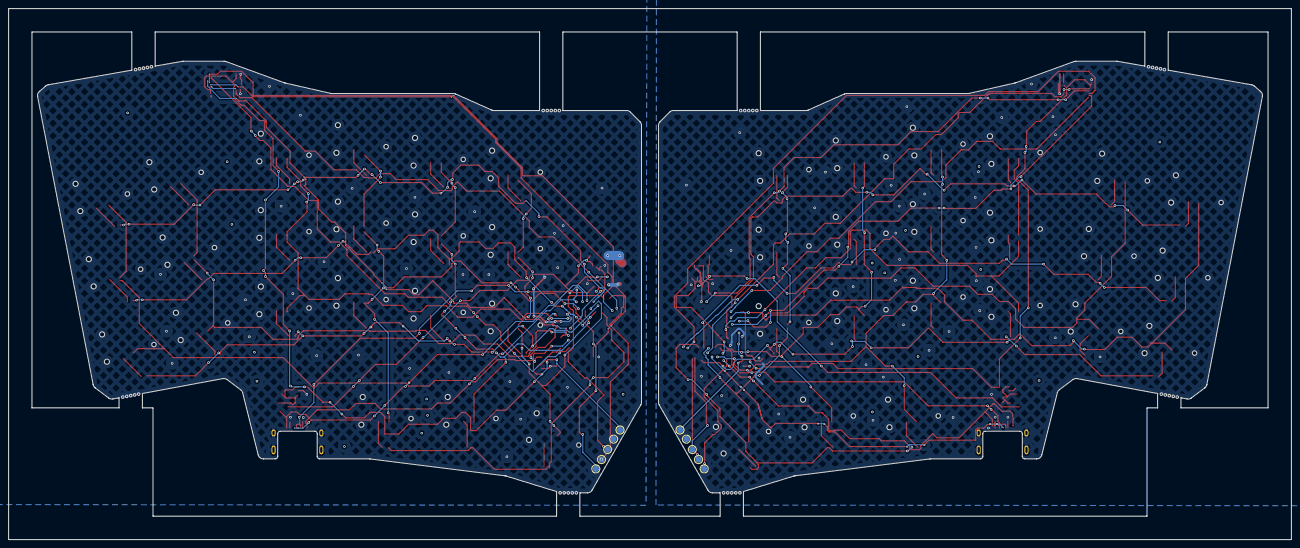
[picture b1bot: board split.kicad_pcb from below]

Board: 2 copper layers, 302.0 x 125.0 mm, 154 parts (10 on the bottom side), 102 nets.

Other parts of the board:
MB1, MB2, MB3, MB4, MB5, MB6, MB7, MB8: Panel_MouseBite_5x0.6_P0.95

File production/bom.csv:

Designator,Footprint,Quantity,Value,LCSC Part #
"C1, C101, C104, C105, C4, C5",0603,6,100n,
"C102, C109, C2, C9",0603,4,2.2uF,
"C103, C3",CAP-SMD_L1.6-W0.8-RD,2,4.7uF 6.3V polymer tantalum,C2158419
"C106, C107, C6, C7",0402,4,1uF,
"C108, C8",0402,2,560pF,
"D1, D101",SOD-323_L1.7-W1.3-LS2.7-RD,2,1N5819WS,C489147
"D10, D102, D103, D104, D105, D106, D107, D108, D109, D11, D110, D111, D112, D113, D114, D115, D116, D117, D118, D119, D12, D120, D121, D122, D13, D14, D15, D16, D17, D18, D19, D2, D20, D21, D22, D3, D4, D5, D6, D7, D8, D9",SOD-523_L1.2-W0.8-LS1.6-RD,42,1N4148WT-7,C83482
"J1, J101",FFC-SMD_10P-P0.50_FH34SRJ-10S-0.5SH,2,LS011B7DH03_FPC,C324723
"OSC1, OSC101",OSC-SMD_4P-L3.2-W1.5,2,X1B0002110001,C256005
"Q102, Q2",SOT-23-3_L3.0-W1.7-P0.95-LS2.9-BR,2,AO3407,C351408
"R1, R101, R102, R2",0402,4,5.1k,
"R103, R108, R3, R8",0402,4,100k,
"R104, R4",0402,2,33.2k,
"R106, R107, R6, R7",0402,4,820k,
"SW1, SW10, SW101, SW102, SW103, SW104, SW105, SW106, SW107, SW108, SW109, SW11, SW110, SW111, SW112, SW113, SW114, SW115, SW116, SW117, SW118, SW119, SW12, SW120, SW121, SW13, SW14, SW15, SW16, SW17, SW18, SW19, SW2, SW20, SW21, SW3, SW4, SW5, SW6, SW7, SW8, SW9",Cherry_ULP_SMD,42,Cherry_ULP_SMD,
TP1,TestPoint_Pad_D1.5mm,1,L_VDD_SYS,
TP101,TestPoint_Pad_D1.5mm,1,R_VDD_SYS,
TP102,TestPoint_Pad_D1.5mm,1,R_GND,
TP103,TestPoint_Pad_D1.5mm,1,R_SWDIO,
TP104,TestPoint_Pad_D1.5mm,1,R_SWDCLK,
TP105,TestPoint_Pad_D1.5mm,1,R_RESET,
TP106,TestPoint_Pad_D2.0mm,1,R_VBAT,
TP107,TestPoint_Pad_D2.0mm,1,R_GND,
TP2,TestPoint_Pad_D1.5mm,1,L_GND,
TP3,TestPoint_Pad_D1.5mm,1,L_SWDIO,
TP4,TestPoint_Pad_D1.5mm,1,L_SWDCLK,
TP5,TestPoint_Pad_D1.5mm,1,L_RESET,
TP6,TestPoint_Pad_D2.0mm,1,L_VBAT,
TP7,TestPoint_Pad_D2.0mm,1,L_GND,
"U1, U101",WIRELM-SMD_E73-2G4M08S1C,2,E73-2G4M08S1C,C356849
"U102, U2",SOT-23-5_L3.0-W1.7-P0.95-LS2.8-BL,2,TP4054,C32574
"U103, U3",SOT-23-5,2,MIC5219-3.0YM5,
"USB1, USB101",USB-C-SMD_SHOU_TYPE-C-16P-CB1.6,2,TYPE-C 16P CB1.6 073,C2906290
